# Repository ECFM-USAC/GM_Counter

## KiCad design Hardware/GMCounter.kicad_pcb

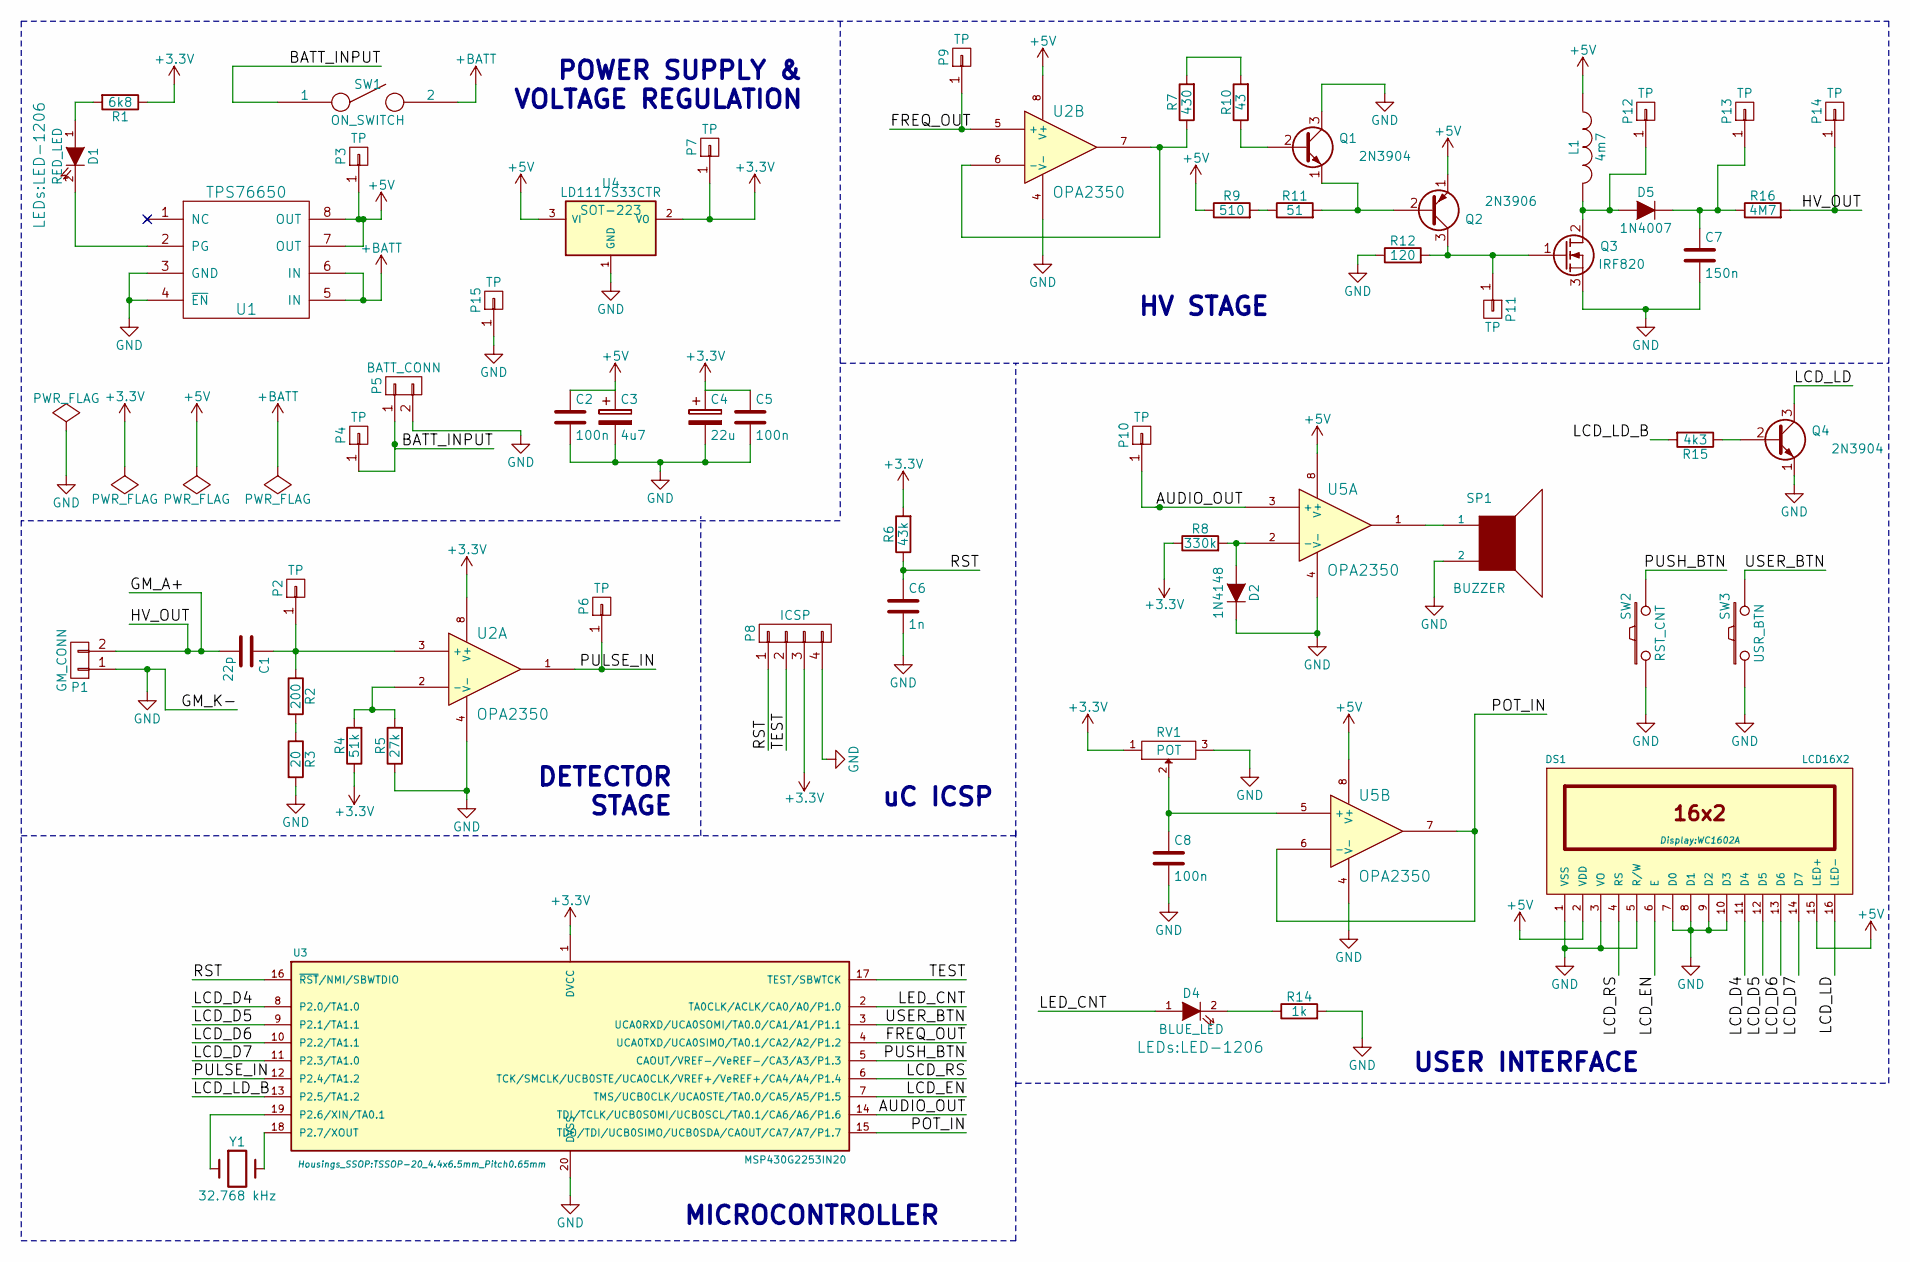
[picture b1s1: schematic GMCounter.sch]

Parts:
C1: 22p; C_0805_HandSoldering
C2, C5, C8: 100n; C_0805_HandSoldering
C3: 4u7; C_Radial_D10_L20_P2.5-5
C4: 22u; C_Radial_D10_L20_P2.5-5
C6: 1n; C_0805_HandSoldering
C7: 150n; C_Rect_L27_W11_P22
D1: RED_LED; LED-1206
D2: 1N4148; Diode_DO-35_SOD27_Horizontal_RM10
D4: BLUE_LED; LED-1206
D5: 1N4007; Diode_DO-41_SOD81_Horizontal_RM10
DS1: LCD16X2; WC1602A
L1: 4m7; Choke_Horizontal_RM25mm
P1: GM_CONN; Pin_Header_Straight_1x02
P2, P3, P4, P6, P7, P9, P10, P11, P12, P13: TP; Measurement_Point_Round-TH_Small
P5: BATT_CONN; Pin_Header_Straight_1x02
P8: ICSP; Pin_Header_Straight_1x04
P14, P15: TP; Pin_Header_Straight_1x01
Q1, Q4: 2N3904; TO-92_Molded_Narrow
Q2: 2N3906; TO-92_Inline_Wide
Q3: IRF820; TO-247_Vertical_Neutral123_largePads
R1: 6k8; R_0805_HandSoldering
R2: 200; R_0805_HandSoldering
R3: 20; R_0805_HandSoldering
R4: 51k; R_0805_HandSoldering
R5: 27k; R_0805_HandSoldering
R6: 43k; R_0805_HandSoldering
R7: 430; R_0805_HandSoldering
R8: 330k; R_0805_HandSoldering
R9: 510; R_0805_HandSoldering
R10: 43; R_0805_HandSoldering
R11: 51; R_0805_HandSoldering
R12: 120; R_0805_HandSoldering
R14: 1k; R_0805_HandSoldering
R15: 4k3; R_0805_HandSoldering
R16: 4M7; Resistor_Horizontal_RM10mm
RV1: POT; Potentiometer_Alps-RK16-single_largePads
SP1: BUZZER; Buzzer_12x9.5RM7.6
SW1: ON_SWITCH; TerminalBlock_Pheonix_MPT-2.54mm_2pol
SW2: RST_CNT; TerminalBlock_Pheonix_MPT-2.54mm_2pol
SW3: USR_BTN; TerminalBlock_Pheonix_MPT-2.54mm_2pol
U1: TPS76650; SOIC-8_3.9x4.9mm_Pitch1.27mm
U2, U5: OPA2350; SOIC-8_3.9x4.9mm_Pitch1.27mm
U3: MSP430G2253IN20; TSSOP-20_4.4x6.5mm_Pitch0.65mm
U4: LD1117S33CTR; SOT-223
Y1: 32.768 kHz; Crystal_Round_Horizontal_3mm_BigPad

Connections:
+BATT: SW1.2, U1.5 (IN), U1.6 (IN)
/AUDIO_OUT: P10.1, U3.14 (TDI/TCLK/UCB0SOMI/UCB0SCL/TA0.1/CA6/A6/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), U5.3 (+)
/BATT_INPUT: P4.1, P5.1, SW1.1
/FREQ_OUT: P9.1, U2.5 (+), U3.4 (UCA0TXD/UCA0SIMO/TA0.1/CA2/A2/P1.2)
/GM_A+: C1.2, P1.2, P14.1, R16.2
/LCD_D4: DS1.11 (D4), U3.8 (P2.0/TA1.0)
/LCD_D5: DS1.12 (D5), U3.9 (P2.1/TA1.1)
/LCD_D6: DS1.13 (D6), U3.10 (P2.2/TA1.1)
/LCD_D7: DS1.14 (D7), U3.11 (P2.3/TA1.0)
/LCD_EN: DS1.6 (E), U3.7 (TMS/UCB0CLK/UCA0STE/TA0.0/CA5/A5/P1.5)
/LCD_LD: DS1.16 (LED-), Q4.3 (C)
/LCD_LD_B: R15.2, U3.13 (P2.5/TA1.2)
/LCD_RS: DS1.4 (RS), U3.6 (TCK/SMCLK/UCB0STE/UCA0CLK/VREF+/VeREF+/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)
/LED_CNT: D4.1 (A), U3.2 (TA0CLK/ACLK/CA0/A0/P1.0)
/POT_IN: U3.15 (TDO/TDI/UCB0SIMO/UCB0SDA/CAOUT/CA7/A7/P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), U5.6 (-), U5.7
/PULSE_IN: P6.1, U2.1, U3.12 (P2.4/TA1.2)
/PUSH_BTN: SW2.2, U3.5 (CAOUT/VREF-/VeREF-/CA3/A3/P1.3)
/RST: C6.1, P8.1, R6.1, U3.16 (~RST~/NMI/SBWTDIO)
/TEST: P8.2, U3.17 (TEST/SBWTCK)
/USER_BTN: SW3.2, U3.3 (UCA0RXD/UCA0SOMI/TA0.0/CA1/A1/P1.1)
GND: C2.2, C3.2, C4.2, C5.2, C6.2, C7.2, C8.2, D2.2 (K), DS1.1 (VSS), DS1.3 (VO), DS1.5 (R/W), DS1.7 (D0), DS1.8 (D1), DS1.9 (D2), DS1.10 (D3), P1.1, P5.2, P8.4, P15.1, Q1.3 (C), Q3.3 (S), Q4.1 (E), R3.2, R5.1, R12.1, R14.2, RV1.3, SP1.2, SW2.1, SW3.1, U1.3 (GND), U1.4 (~EN), U2.4 (V-), U3.20 (DVSS), U4.1 (GND), U5.4 (V-); also elsewhere on the board
unnamed: C1.1, P2.1, R2.1, U2.3 (+)
unnamed: C7.1, D5.2 (K), P13.1, R16.1
unnamed: C8.1, RV1.2, U5.5 (+)
unnamed: D1.1 (A), R1.2
unnamed: D1.2 (K), U1.2 (PG)
unnamed: D2.1 (A), R8.2, U5.2 (-)
unnamed: D4.2 (K), R14.1
unnamed: D5.1 (A), L1.2, P12.1, Q3.2 (D)
unnamed: P11.1, Q2.3 (C), Q3.1 (G), R12.2
unnamed: Q1.1 (E), Q2.2 (B), R11.2
unnamed: Q1.2 (B), R10.1
unnamed: Q4.2 (B), R15.1
unnamed: R2.2, R3.1
unnamed: R4.2, R5.2, U2.2 (-)
unnamed: R7.1, U2.6 (-), U2.7
unnamed: R7.2, R10.2
unnamed: R9.2, R11.1
unnamed: SP1.1, U5.1
unnamed: U3.18 (P2.7/XOUT), Y1.2
unnamed: U3.19 (P2.6/XIN/TA0.1), Y1.1

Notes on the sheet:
HV STAGE
USER INTERFACE
POWER SUPPLY & VOLTAGE REGULATION
DETECTOR STAGE
uC ICSP
MICROCONTROLLER

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
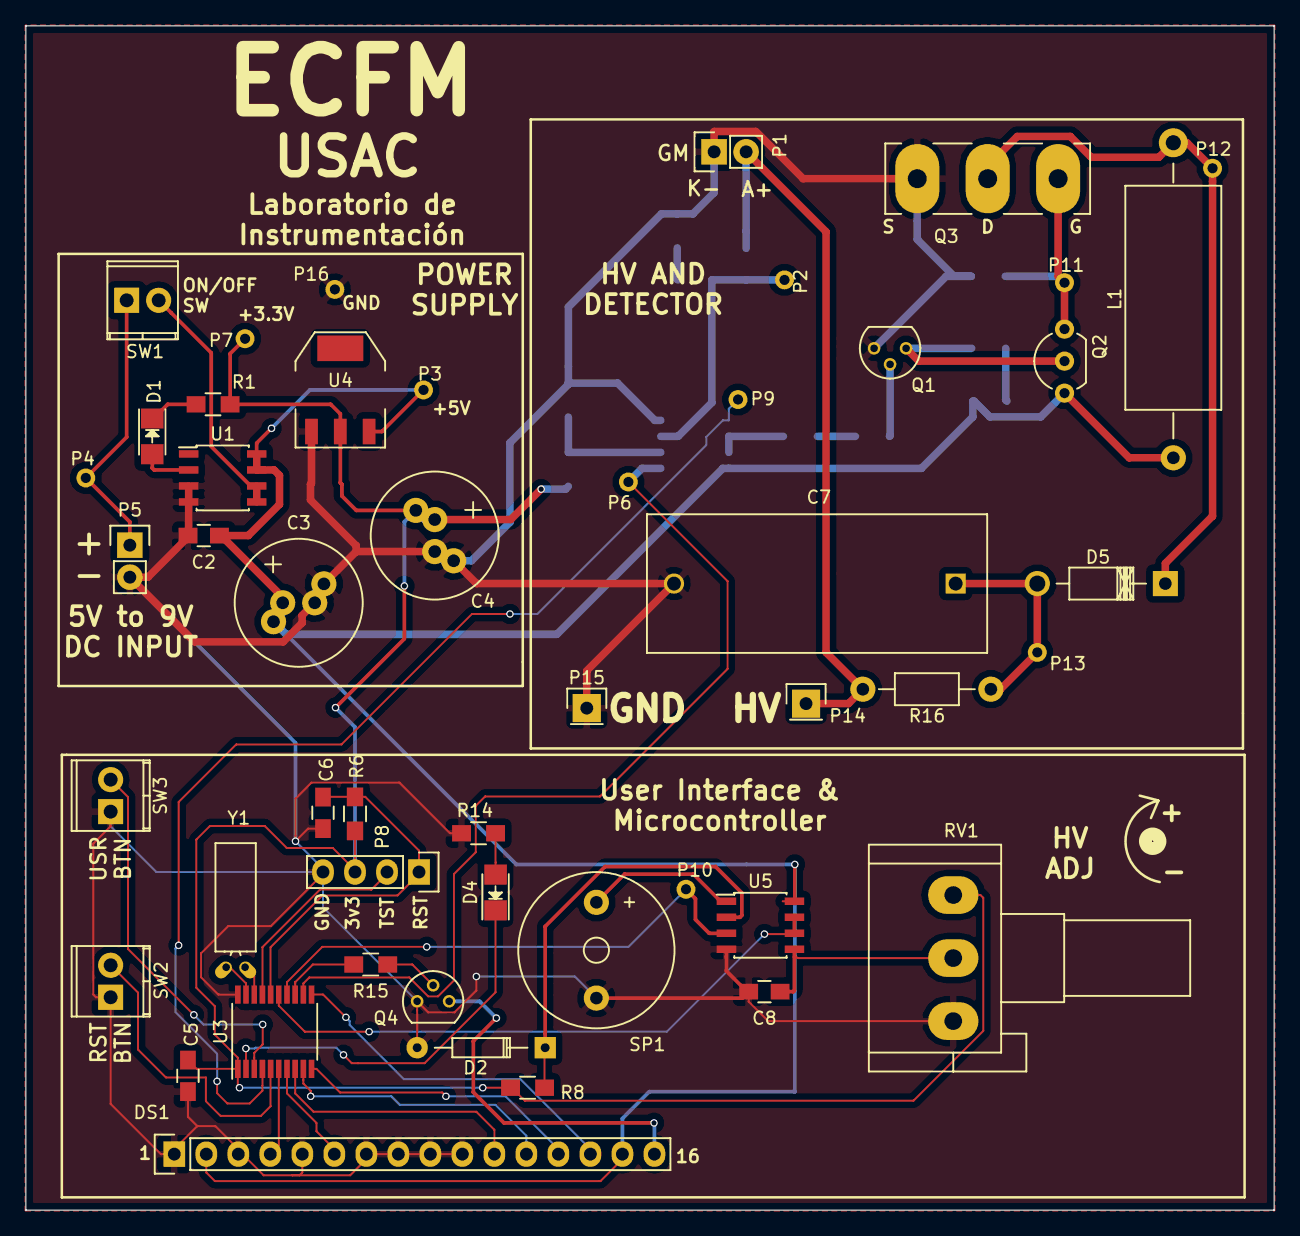
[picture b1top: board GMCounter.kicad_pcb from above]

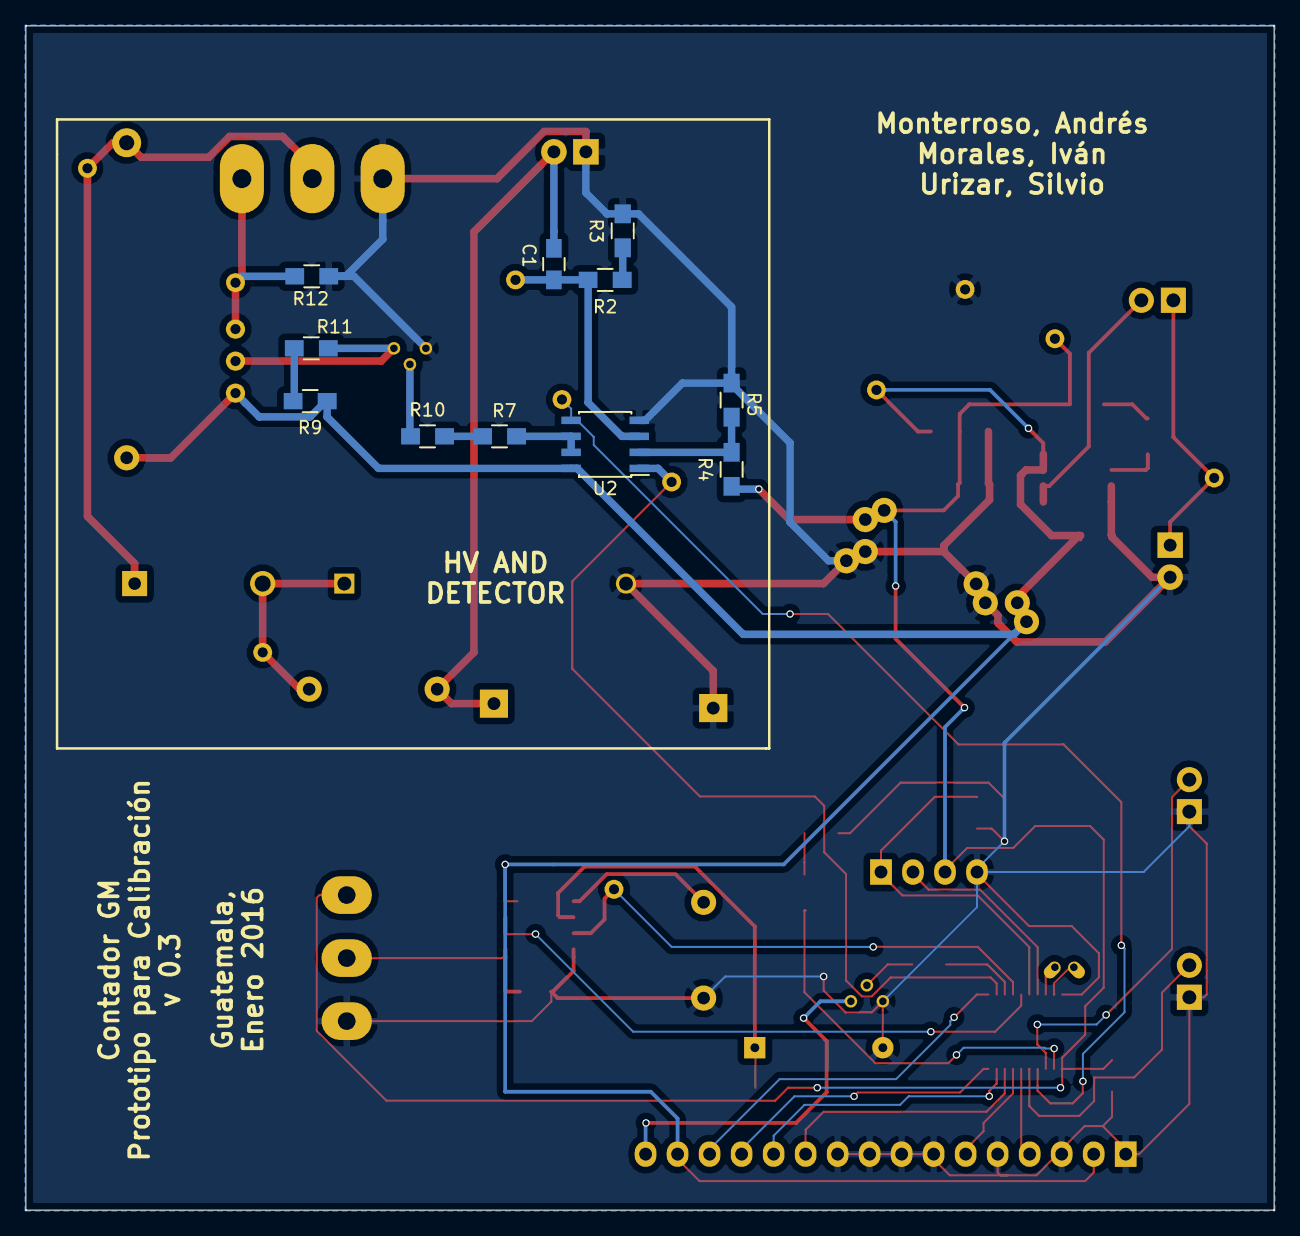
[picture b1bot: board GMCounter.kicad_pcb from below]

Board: 2 copper layers, 99.1 x 94.0 mm, 60 parts (11 on the bottom side), 43 nets.

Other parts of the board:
P16: TP; Measurement_Point_Round-TH_Small

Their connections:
GND: P16.1; also elsewhere on the board

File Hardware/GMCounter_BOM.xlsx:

ref | value5 | footprint | part
C1 | 22p | Capacitors_SMD:C_0805_HandSoldering | C
C2 | 100n | Capacitors_SMD:C_0805_HandSoldering | C
C3 | 4u7 | Capacitors_ThroughHole:C_Radial_D10_L20_P2.5-5 | CP
C4 | 22u | Capacitors_ThroughHole:C_Radial_D10_L20_P2.5-5 | CP
C5 | 100n | Capacitors_SMD:C_0805_HandSoldering | C
C6 | 1n | Capacitors_SMD:C_0805_HandSoldering | C
C7 | 150n | Capacitors_ThroughHole:C_Rect_L27_W11_P22 | C
C8 | 100n | Capacitors_SMD:C_0805_HandSoldering | C
D1 | RED_LED | LEDs:LED-1206 | LED-RESCUE-GMCounter
D2 | 1N4148 | Diodes_ThroughHole:Diode_DO-35_SOD27_Horizontal_RM10 | D-RESCUE-GMCounter
D4 | BLUE_LED | LEDs:LED-1206 | LED-RESCUE-GMCounter
D5 | 1N4007 | Diodes_ThroughHole:Diode_DO-41_SOD81_Horizontal_RM10 | D-RESCUE-GMCounter
DS1 | LCD16X2 | Socket_Strips:Socket_Strip_Straight_1x16 | LCD16X2
L1 | 4m7 | Choke_Axial_ThroughHole:Choke_Horizontal_RM25mm | INDUCTOR
P1 | GM_CONN | Pin_Headers:Pin_Header_Straight_1x02 | CONN_01X02
P10 | TP | Measurement_Points:Measurement_Point_Round-TH_Small | CONN_01X01
P11 | TP | Measurement_Points:Measurement_Point_Round-TH_Small | CONN_01X01
P12 | TP | Measurement_Points:Measurement_Point_Round-TH_Small | CONN_01X01
P13 | TP | Measurement_Points:Measurement_Point_Round-TH_Small | CONN_01X01
P14 | TP | Pin_Headers:Pin_Header_Straight_1x01 | CONN_01X01
P15 | TP | Pin_Headers:Pin_Header_Straight_1x01 | CONN_01X01
P16 | TP | Measurement_Points:Measurement_Point_Round-TH_Small | CONN_01X01
P2 | TP | Measurement_Points:Measurement_Point_Round-TH_Small | CONN_01X01
P3 | TP | Measurement_Points:Measurement_Point_Round-TH_Small | CONN_01X01
P4 | TP | Measurement_Points:Measurement_Point_Round-TH_Small | CONN_01X01
P5 | BATT_CONN | Pin_Headers:Pin_Header_Straight_1x02 | CONN_01X02
P6 | TP | Measurement_Points:Measurement_Point_Round-TH_Small | CONN_01X01
P7 | TP | Measurement_Points:Measurement_Point_Round-TH_Small | CONN_01X01
P8 | ICSP | Pin_Headers:Pin_Header_Straight_1x04 | CONN_01X04
P9 | TP | Measurement_Points:Measurement_Point_Round-TH_Small | CONN_01X01
Q1 | 2N3904 | Housings_TO-92:TO-92_Molded_Narrow | Q_NPN_EBC-RESCUE-GMCounter
Q2 | 2N3906 | Housings_TO-92:TO-92_Inline_Wide | Q_PNP_EBC-RESCUE-GMCounter
Q3 | IRF820 | TO_SOT_Packages_THT:TO-247_Vertical_Neutral123_largePads | Q_NMOS_GDS-RESCUE-GMCounter
Q4 | 2N3904 | Housings_TO-92:TO-92_Molded_Narrow | Q_NPN_EBC-RESCUE-GMCounter
R1 | 6k8 | Resistors_SMD:R_0805_HandSoldering | R
R10 | 43 | Resistors_SMD:R_0805_HandSoldering | R
R11 | 51 | Resistors_SMD:R_0805_HandSoldering | R
R12 | 120 | Resistors_SMD:R_0805_HandSoldering | R
R14 | 1k | Resistors_SMD:R_0805_HandSoldering | R
R15 | 4k3 | Resistors_SMD:R_0805_HandSoldering | R
R16 | 4M7 | Resistors_ThroughHole:Resistor_Horizontal_RM10mm | R
R2 | 200 | Resistors_SMD:R_0805_HandSoldering | R
R3 | 20 | Resistors_SMD:R_0805_HandSoldering | R
R4 | 51k | Resistors_SMD:R_0805_HandSoldering | R
R5 | 27k | Resistors_SMD:R_0805_HandSoldering | R
R6 | 43k | Resistors_SMD:R_0805_HandSoldering | R
R7 | 430 | Resistors_SMD:R_0805_HandSoldering | R
R8 | 330k | Resistors_SMD:R_0805_HandSoldering | R
R9 | 510 | Resistors_SMD:R_0805_HandSoldering | R
RV1 | POT | Potentiometers:Potentiometer_Alps-RK16-single_largePads | POT
SP1 | BUZZER | Buzzers_Beepers:Buzzer_12x9.5RM7.6 | SPEAKER
SW1 | ON_SWITCH | Terminal_Blocks:TerminalBlock_Pheonix_MPT-2.54mm_2pol | SPST
SW2 | RST_CNT | Terminal_Blocks:TerminalBlock_Pheonix_MPT-2.54mm_2pol | SW_PUSH
SW3 | USR_BTN | Terminal_Blocks:TerminalBlock_Pheonix_MPT-2.54mm_2pol | SW_PUSH
U1 | TPS76650 | Housings_SOIC:SOIC-8_3.9x4.9mm_Pitch1.27mm | TPS76650
U2 | OPA2350 | Housings_SOIC:SOIC-8_3.9x4.9mm_Pitch1.27mm | OPA2350
U3 | MSP430G2253IN20 | Housings_SSOP:TSSOP-20_4.4x6.5mm_Pitch0.65mm | MSP430G2253IN20
U4 | LD1117S33CTR | SOT-223 | LD1117S33CTR
U5 | OPA2350 | Housings_SOIC:SOIC-8_3.9x4.9mm_Pitch1.27mm | OPA2350
Y1 | 32.768 kHz | Crystals:Crystal_Round_Horizontal_3mm_BigPad | Crystal

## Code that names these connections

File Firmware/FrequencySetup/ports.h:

//----------- PIN DEFINITIONS --------------

#ifndef PORTS_H_
#define PORTS_H_

//--------------- PORT 1 ---------------
#define LED_OK    (0x0001); //P1.0
#define USER_BTN  (0x0002); //P1.1
#define FREQ_OUT  (0x0004); //P1.2
#define PUSH_BTN  (0x0008); //P1.3
#define SOUND_OUT (0x0040); //P1.6

//--------------- PORT 2 ---------------
#define PULSE_IN  (0x0010); //P2.4
#define LCD_LED   (0x0020); //P2.5

//--------------- LCD ------------------
//At least, LCD_Dx bits must be in the same port (either P2 or P1)

#define LCD_RS	(0x0010); //P1.4
#define LCD_EN	(0x0020); //P1.5
#define LCD_D4	(0x0001); //P2.0
#define LCD_D5	(0x0002); //P2.1
#define LCD_D6	(0x0004); //P2.2
#define LCD_D7	(0x0008); //P2.3

#endif /* PORTS_H_ */

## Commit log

2015-08-12 :tada: Added .gitattributes
2015-08-12 Frequency generator with Energia on MSP430
    Change frequency with PUSH2. Red LED will glow when frequency is within
    desired range.
2015-08-26 Added interrupt capability and audio output
    Basic GM Counter. Not displaying value, just making some nice GM-like
    sound within radiation presence. Tested with Sr-90 source.
2015-08-31 Frequency values for HV generation
2015-09-25 Initial commit - Frequency Setup Function now working
2015-09-25 PWM without interrupts
2015-09-25 Frequency set to 2 kHz Geiger-like sound
2015-09-25 Preliminary PCB design
2015-09-27 Parameters set back to accomplish HV Generation requirements
2015-09-27 First successful LCD 16x2 test
2015-09-28 Now displaying current HVfrequency
    - LPM0 implemented (shouldn't it work with LPM1?)
    - Interrupt-driven push-button
2015-09-28 .gitignore first commit
2015-09-29 Sound and HV Frequency implemented simultaneously
    HV Frequency not using interrrupts
    Sound ain't using interrupts either. However, TA1CCR2 interrupt has been
    implemented to count how many "sound cycles" run before turning sound
    off.
    --------------- SOUND NOT WORKING YET --------------------
    Should debug TA1CCR2 Interrupts
2015-09-29 Common-cathod speaker and SoundOut Working Nice :+1: :smiley:
2015-10-04 Sound generation sharing HV pwm signal
    This test was done to show how both signals may be independent, but
    relay on the same timer TA0 and comparator but enabling/disabling
    distinct port outputs. It's intended to be implemented on the main
    firmware project
2015-10-04 Cleaning unused files
2015-10-04 Cleaned up files again
2015-10-04 'ticks' counter now is descending
    And test inside interrupt checks whether counter is zero or not
    (increasing power-saving capabilites)
2015-10-05 Sound and HV implemented on same TimerA0
    Timer1_A3 available now to implement RTC with ACLK from 32.768kHz quartz
    crystal.
2015-10-06 Quartz XTAL as 1 second tick timer working nice!
2015-10-07 Xtal interrupt implemented
    Must implement moving-average algorithm. Current implementation is
    wrong.
2015-10-08 IDE trash
2015-10-12 Implemented button debouncing with WDT+
2015-10-12 Implemented debouncing with WDT+
    Implemented in a new project. Now, it should be integrated to the
    existing project.
2015-10-15 Implemented LCD LED control on/off
    Not tested yet.
    New I/O:
    USER_BTN <INPUT> @ P1.1
    LCD_LED <OUTPUT> @ P2.5
2015-10-19 LCD LED control implemented. Has an issue
    Issue: LED keeps turning on on each PULSE_IN interrupt. It seems to be a
    HARDWARE issue.
2015-10-21 LCD's LED Controller now working nice!
2015-10-21 Started PCB design over again
2015-10-22 Working on schematics
2015-10-23 First complete schematic commit
2015-11-03 Components Library added
2015-11-12 Reviewed Schematic Design
    Using SMD passive devices
2016-01-11 Resync
2016-01-15 Updated preliminary PCB design with ECFM logo
2016-01-18 First calibration hardware design commit
2016-01-20 ADC Configuration Test Done with TMR0_CCR1
2016-01-21 ADC Calibration Firmware First Commit
    PCB hasn't been modified yet.
2016-01-21 Schematic design now includes potentiometer
    Netlist has been exported, but it hasn't been imported to PCB yet
2016-01-21 Netlist updated
2016-01-22 PCB Release Candidate
2016-01-28 PCB Release Candidate
    v 0.3
2016-02-04 PCB Submission to SeeedStudio
2016-04-06 BOM for PCB Manufacturing
2016-04-06 Revert "BOM for PCB Manufacturing"
    This reverts commit cf9e08cf3c7c7d2e8a3dd81d4616a5fa6d17cc17.
2016-05-06 Fixed backlight bug and reverse HV voltage adj
2016-05-18 Tuned for 650V HV output
